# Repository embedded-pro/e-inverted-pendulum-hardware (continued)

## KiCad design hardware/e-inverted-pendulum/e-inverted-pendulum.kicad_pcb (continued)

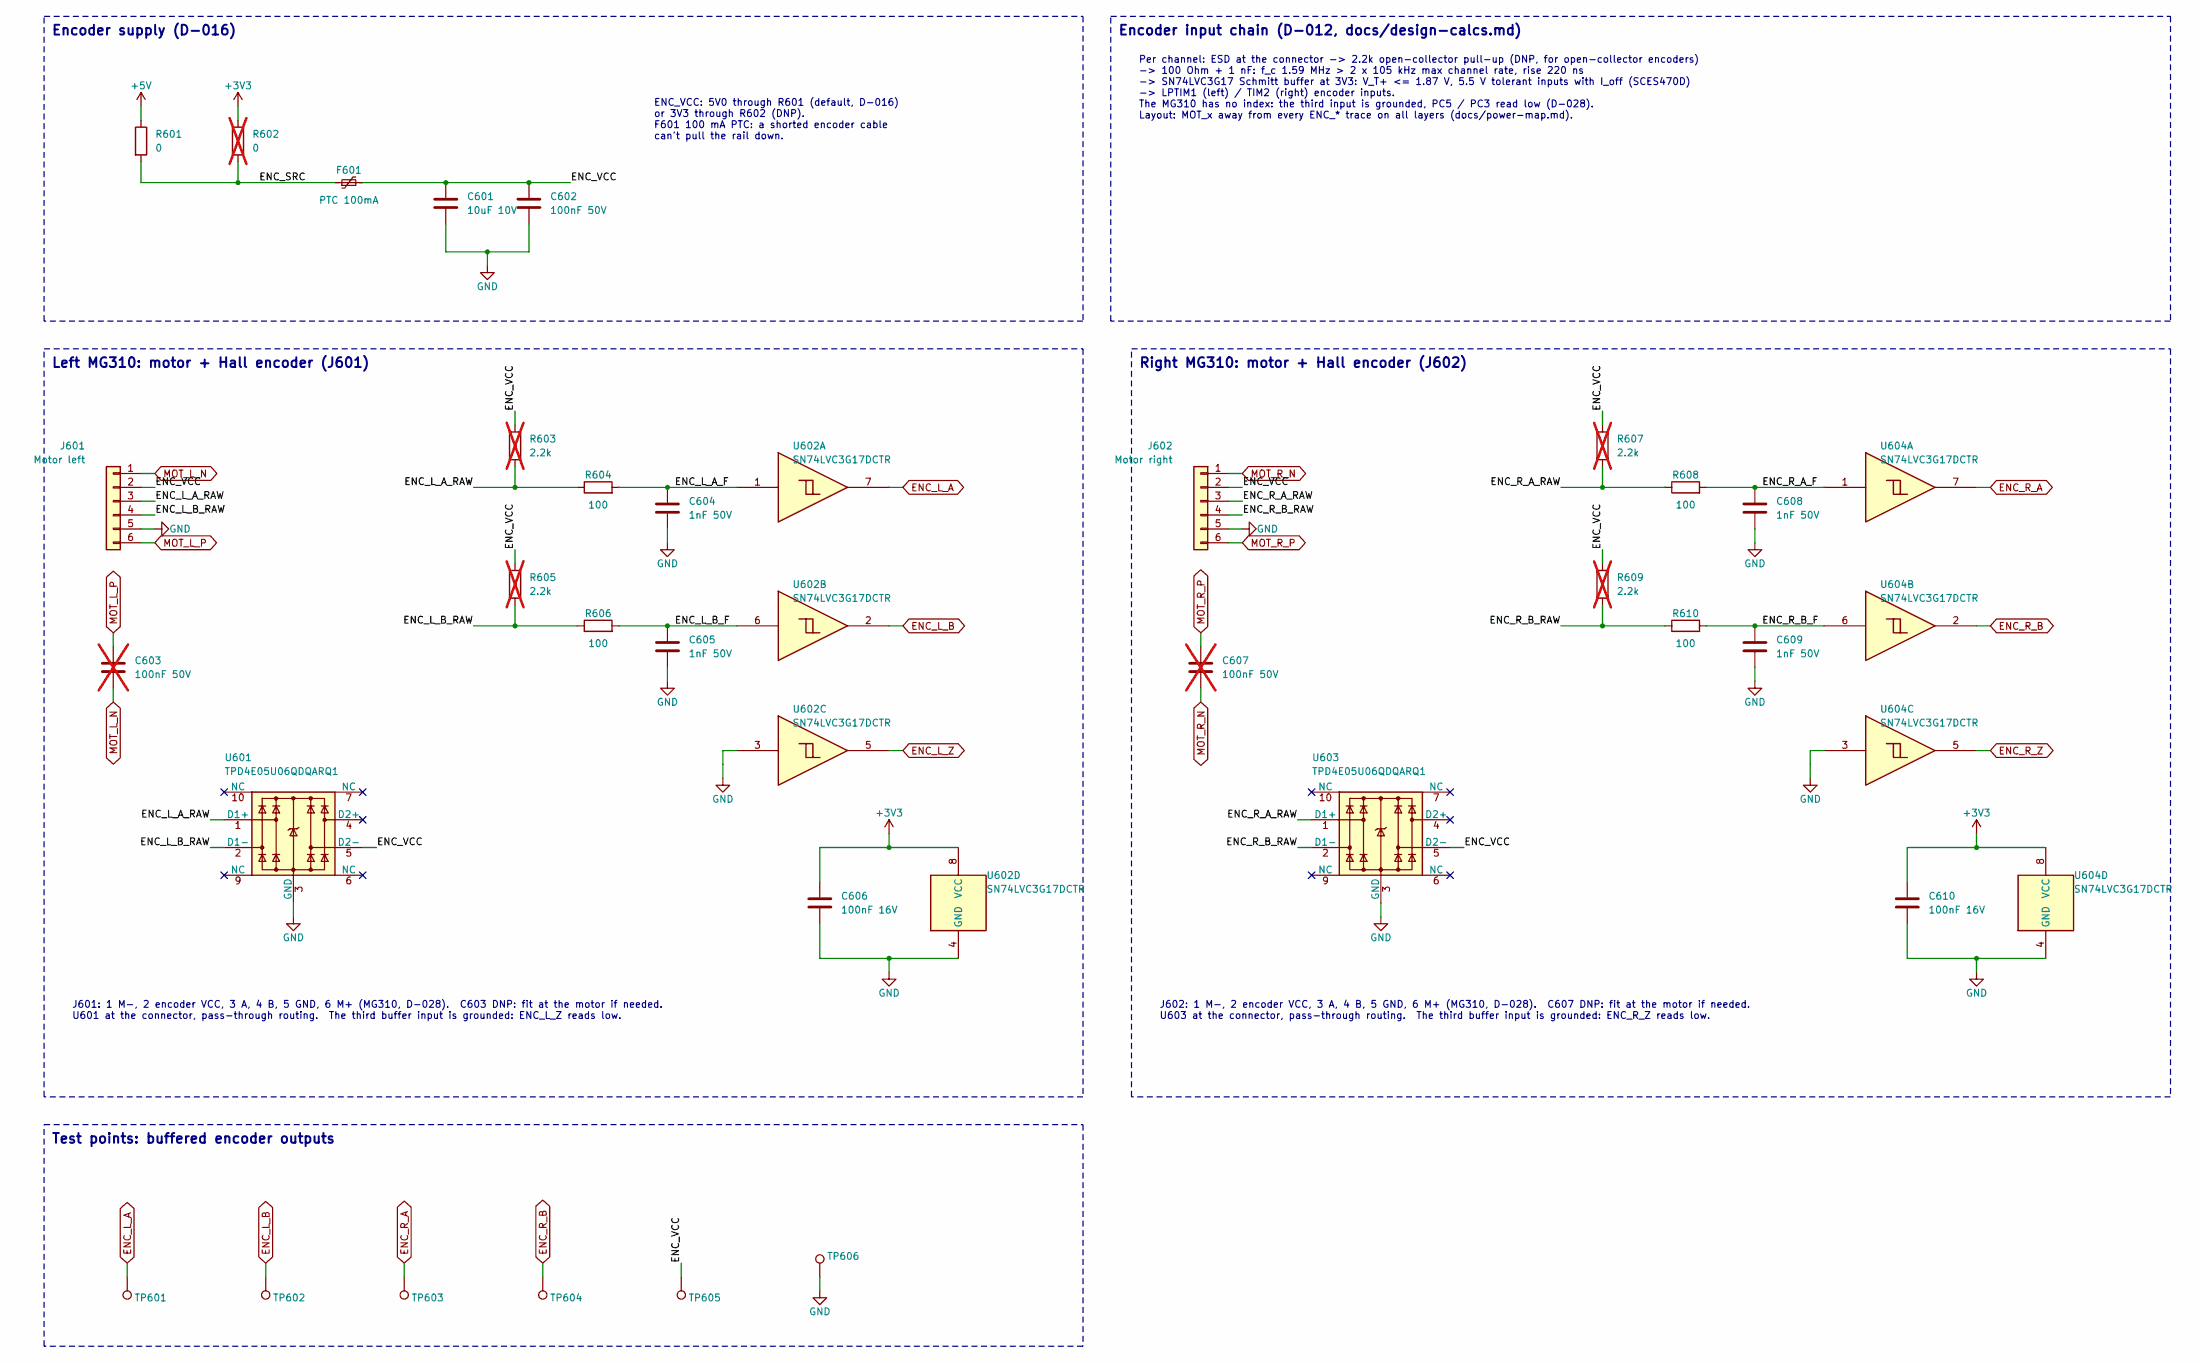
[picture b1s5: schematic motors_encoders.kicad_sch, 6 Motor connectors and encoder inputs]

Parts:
C601: 10uF 10V; C_0603_1608Metric; MPN CL10A106KP8NNNC; LCSC C19702
C602: 100nF 50V; C_0603_1608Metric; MPN CC0603KRX7R9BB104; LCSC C14663
C603, C607: 100nF 50V; C_0603_1608Metric; MPN CC0603KRX7R9BB104; LCSC C14663; not fitted
C604, C605, C608, C609: 1nF 50V; C_0603_1608Metric; MPN CL10B102KB8NNNC; LCSC C1588
C606, C610: 100nF 16V; C_0402_1005Metric; MPN CL05B104KO5NNNC; LCSC C1525
F601: PTC 100mA; Fuse_0805_2012Metric; MPN SMD0805P010TF; LCSC C20975
J601: Motor left; JST_PH_S6B-PH-K_1x06_P2.00mm_Horizontal; MPN S6B-PH-K-S(LF)(SN); LCSC C157920
J602: Motor right; JST_PH_S6B-PH-K_1x06_P2.00mm_Horizontal; MPN S6B-PH-K-S(LF)(SN); LCSC C157920
R601: 0; R_0603_1608Metric; MPN 0603WAF0000T5E; LCSC C21189
R602: 0; R_0603_1608Metric; MPN 0603WAF0000T5E; LCSC C21189; not fitted
R603, R605, R607, R609: 2.2k; R_0603_1608Metric; MPN 0603WAF2201T5E; LCSC C4190; not fitted
R604, R606, R608, R610: 100; R_0603_1608Metric; MPN 0603WAF1000T5E; LCSC C22775
TP601: ENC_L_A; TestPoint_Pad_D1.0mm
TP602: ENC_L_B; TestPoint_Pad_D1.0mm
TP603: ENC_R_A; TestPoint_Pad_D1.0mm
TP604: ENC_R_B; TestPoint_Pad_D1.0mm
TP605: ENC_VCC; TestPoint_Pad_D1.5mm
TP606: GND; TestPoint_Pad_D1.5mm
U601, U603: TPD4E05U06QDQARQ1; USON-10_2.5x1.0mm_P0.5mm; MPN TPD4E05U06QDQARQ1; LCSC C81353
U602, U604: SN74LVC3G17DCTR; SSOP-8_2.95x2.8mm_P0.65mm; MPN SN74LVC3G17DCTR; LCSC C18213

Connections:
+3V3: C606.1, C610.1, R602.1, U602.8 (VCC), U604.8 (VCC); also elsewhere on the board
+5V: R601.1; also elsewhere on the board
/6 Motor connectors and encoder inputs/ENC_L_A_F: C604.1, R604.2, U602.1
/6 Motor connectors and encoder inputs/ENC_L_A_RAW: J601.3, R603.1, R604.1, U601.1 (D1+)
/6 Motor connectors and encoder inputs/ENC_L_B_F: C605.1, R606.2, U602.6
/6 Motor connectors and encoder inputs/ENC_L_B_RAW: J601.4, R605.1, R606.1, U601.2 (D1-)
/6 Motor connectors and encoder inputs/ENC_R_A_F: C608.1, R608.2, U604.1
/6 Motor connectors and encoder inputs/ENC_R_A_RAW: J602.3, R607.1, R608.1, U603.1 (D1+)
/6 Motor connectors and encoder inputs/ENC_R_B_F: C609.1, R610.2, U604.6
/6 Motor connectors and encoder inputs/ENC_R_B_RAW: J602.4, R609.1, R610.1, U603.2 (D1-)
/6 Motor connectors and encoder inputs/ENC_SRC: F601.1, R601.2, R602.2
/6 Motor connectors and encoder inputs/ENC_VCC: C601.1, C602.1, F601.2, J601.2, J602.2, R603.2, R605.2, R607.2, R609.2, TP605.1, U601.5 (D2-), U603.5 (D2-)
ENC_L_A: TP601.1, U602.7; also elsewhere on the board
ENC_L_B: TP602.1, U602.2; also elsewhere on the board
ENC_L_Z: U602.5; also elsewhere on the board
ENC_R_A: TP603.1, U604.7; also elsewhere on the board
ENC_R_B: TP604.1, U604.2; also elsewhere on the board
ENC_R_Z: U604.5; also elsewhere on the board
GND: C601.2, C602.2, C604.2, C605.2, C606.2, C608.2, C609.2, C610.2, J601.5, J602.5, TP606.1, U601.3 (GND), U601.8 (GND), U602.3, U602.4 (GND), U603.3 (GND), U603.8 (GND), U604.3, U604.4 (GND); also elsewhere on the board
MOT_L_N: C603.2, J601.1; also elsewhere on the board
MOT_L_P: C603.1, J601.6; also elsewhere on the board
MOT_R_N: C607.2, J602.1; also elsewhere on the board
MOT_R_P: C607.1, J602.6; also elsewhere on the board

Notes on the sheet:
Per channel: ESD at the connector -> 2.2k open-collector pull-up (DNP, for open-collector encoders) -> 100 Ohm + 1 nF: f_c 1.59 MHz > 2 x 105 kHz max channel rate, rise 220 ns -> SN74LVC3G17 Schmitt buffer at 3V3: V_T+ <= 1.87 V, 5.5 V tolerant inputs with I_off (SCES470D) -> LPTIM1 (left) / TIM2 (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
Right MG310: motor + Hall encoder (J602)
J602: 1 M-, 2 encoder VCC, 3 A, 4 B, 5 GND, 6 M+ (MG310, D-028). C607 DNP: fit at the motor if needed. U603 at the connector, pass-through routing. The third buffer input is grounded: ENC_R_Z reads low.
J601: 1 M-, 2 encoder VCC, 3 A, 4 B, 5 GND, 6 M+ (MG310, D-028). C603 DNP: fit at the motor if needed. U601 at the connector, pass-through routing. The third buffer input is grounded: ENC_L_Z reads low.
Encoder input chain (D-012, docs/design-calcs.md)
ENC_VCC: 5V0 through R601 (default, D-016) or 3V3 through R602 (DNP). F601 100 mA PTC: a shorted encoder cable can't pull the rail down.
Left MG310: motor + Hall encoder (J601)
Test points: buffered encoder outputs
Encoder supply (D-016)

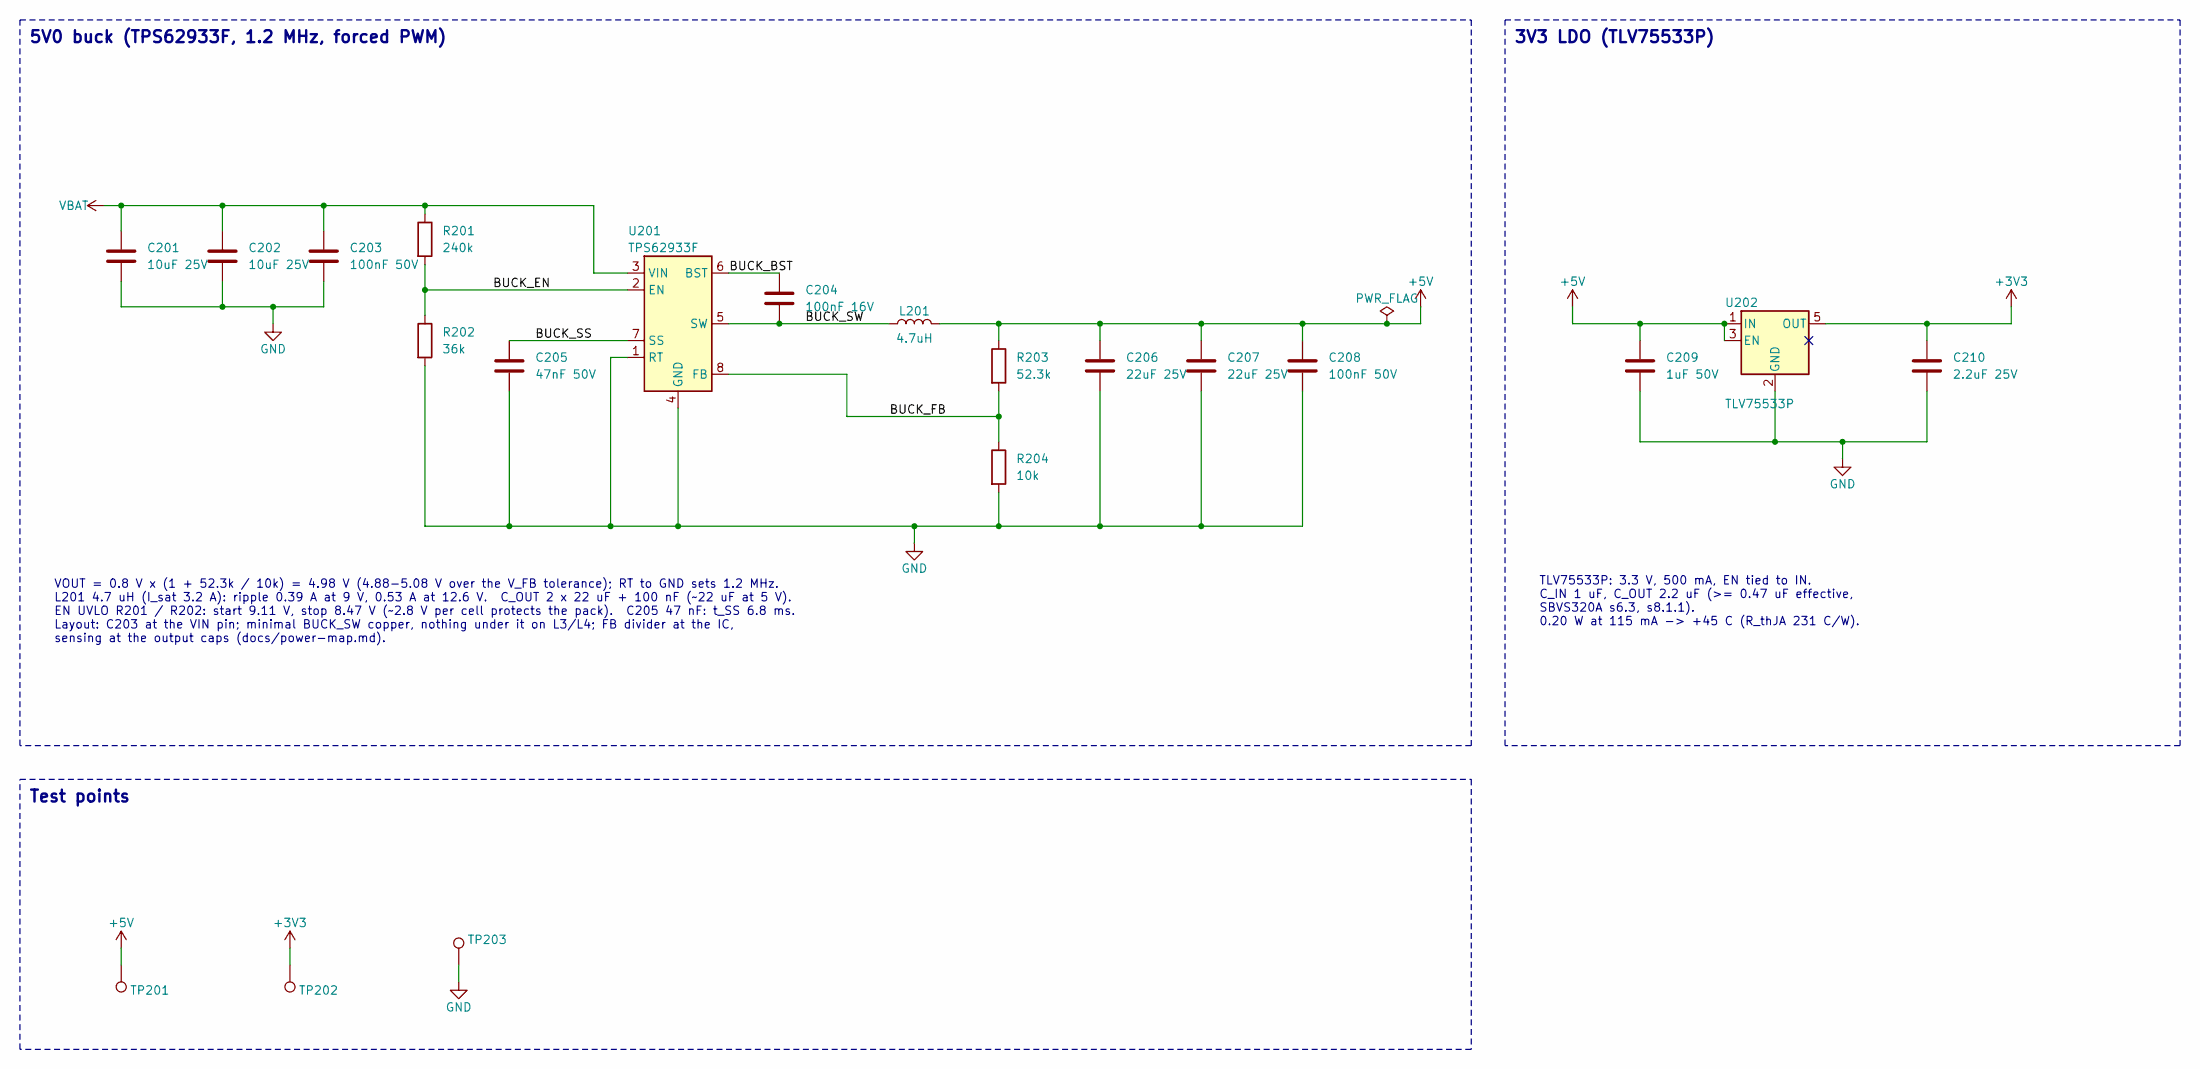
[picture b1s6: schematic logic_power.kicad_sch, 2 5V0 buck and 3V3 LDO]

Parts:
C201, C202: 10uF 25V; C_0805_2012Metric; MPN CL21A106KAYNNNE; LCSC C15850
C203, C208: 100nF 50V; C_0603_1608Metric; MPN CC0603KRX7R9BB104; LCSC C14663
C204: 100nF 16V; C_0402_1005Metric; MPN CL05B104KO5NNNC; LCSC C1525
C205: 47nF 50V; C_0603_1608Metric; MPN CL10B473KB8NNNC; LCSC C1622
C206, C207: 22uF 25V; C_0805_2012Metric; MPN CL21A226MAQNNNE; LCSC C45783
C209: 1uF 50V; C_0603_1608Metric; MPN CL10A105KB8NNNC; LCSC C15849
C210: 2.2uF 25V; C_0603_1608Metric; MPN CL10A225KO8NNNC; LCSC C23630
L201: 4.7uH; L_Sunlord_SWPA4030S; MPN SWPA4030S4R7MT; LCSC C57269
R201: 240k; R_0603_1608Metric; MPN 0603WAF2403T5E; LCSC C4197
R202: 36k; R_0603_1608Metric; MPN 0603WAF3602T5E; LCSC C23147
R203: 52.3k; R_0603_1608Metric; MPN 0603WAF5232T5E; LCSC C23198
R204: 10k; R_0603_1608Metric; MPN 0603WAF1002T5E; LCSC C25804
TP201: +5V; TestPoint_Pad_D1.5mm
TP202: +3V3; TestPoint_Pad_D1.5mm
TP203: GND; TestPoint_Pad_D1.5mm
U201: TPS62933F; SOT-583-8; MPN TPS62933FDRLR; LCSC C5219272
U202: TLV75533P; SOT-23-5; MPN TLV75533PDBVR; LCSC C404027

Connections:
+3V3: C210.1, TP202.1, U202.5 (OUT); also elsewhere on the board
+5V: C206.1, C207.1, C208.1, C209.1, L201.2, R203.1, TP201.1, U202.1 (IN), U202.3 (EN); also elsewhere on the board
/2 5V0 buck and 3V3 LDO/BUCK_BST: C204.1, U201.6 (BST)
/2 5V0 buck and 3V3 LDO/BUCK_EN: R201.2, R202.1, U201.2 (EN)
/2 5V0 buck and 3V3 LDO/BUCK_FB: R203.2, R204.1, U201.8 (FB)
/2 5V0 buck and 3V3 LDO/BUCK_SS: C205.1, U201.7 (SS)
/2 5V0 buck and 3V3 LDO/BUCK_SW: C204.2, L201.1, U201.5 (SW)
GND: C201.2, C202.2, C203.2, C205.2, C206.2, C207.2, C208.2, C209.2, C210.2, R202.2, R204.2, TP203.1, U201.1 (RT), U201.4 (GND), U202.2 (GND); also elsewhere on the board
VBAT: C201.1, C202.1, C203.1, R201.1, U201.3 (VIN); also elsewhere on the board

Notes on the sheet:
VOUT = 0.8 V x (1 + 52.3k / 10k) = 4.98 V (4.88-5.08 V over the V_FB tolerance); RT to GND sets 1.2 MHz. L201 4.7 uH (I_sat 3.2 A): ripple 0.39 A at 9 V, 0.53 A at 12.6 V. C_OUT 2 x 22 uF + 100 nF (~22 uF at 5 V). EN UVLO R201 / R202: start 9.11 V, stop 8.47 V (~2.8 V per cell protects the pack). C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
3V3 LDO (TLV75533P)
TLV75533P: 3.3 V, 500 mA, EN tied to IN. C_IN 1 uF, C_OUT 2.2 uF (>= 0.47 uF effective, SBVS320A s6.3, s8.1.1). 0.20 W at 115 mA -> +45 C (R_thJA 231 C/W).
Test points
5V0 buck (TPS62933F, 1.2 MHz, forced PWM)

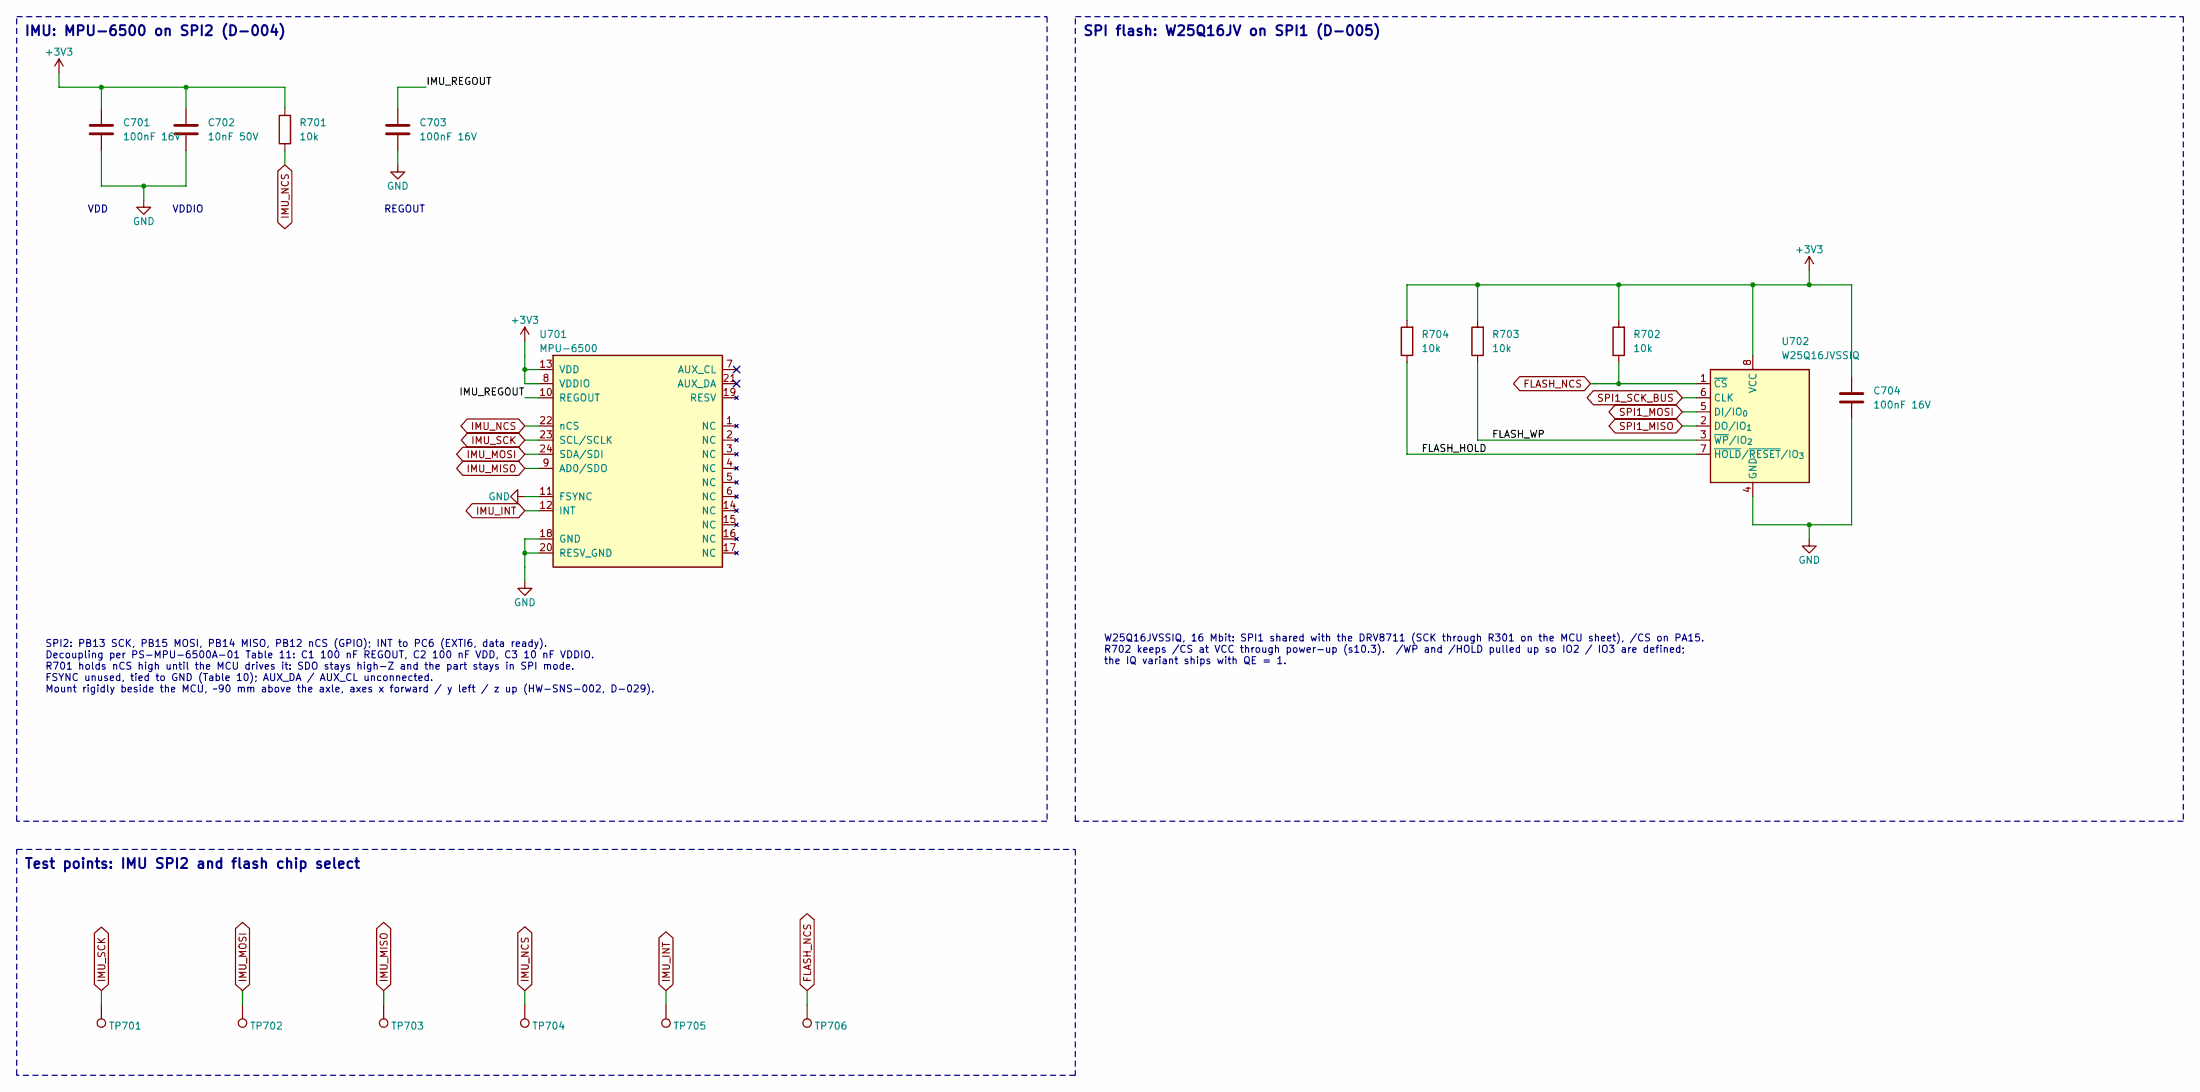
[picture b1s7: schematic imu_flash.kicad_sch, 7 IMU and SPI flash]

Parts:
C701, C703, C704: 100nF 16V; C_0402_1005Metric; MPN CL05B104KO5NNNC; LCSC C1525
C702: 10nF 50V; C_0603_1608Metric; MPN CL10B103KB8NNNC; LCSC C1589
R701, R702, R703, R704: 10k; R_0603_1608Metric; MPN 0603WAF1002T5E; LCSC C25804
TP701: IMU_SCK; TestPoint_Pad_D1.0mm
TP702: IMU_MOSI; TestPoint_Pad_D1.0mm
TP703: IMU_MISO; TestPoint_Pad_D1.0mm
TP704: IMU_NCS; TestPoint_Pad_D1.0mm
TP705: IMU_INT; TestPoint_Pad_D1.0mm
TP706: FLASH_NCS; TestPoint_Pad_D1.0mm
U701: MPU-6500; InvenSense_QFN-24_3x3mm_P0.4mm; MPN MPU-6500; LCSC C50278
U702: W25Q16JVSSIQ; SOIC-8_5.3x5.3mm_P1.27mm; MPN W25Q16JVSSIQ; LCSC C131025

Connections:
+3V3: C701.1, C702.1, C704.1, R701.2, R702.2, R703.2, R704.2, U701.8 (VDDIO), U701.13 (VDD), U702.8 (VCC); also elsewhere on the board
/7 IMU and SPI flash/FLASH_HOLD: R704.1, U702.7 (~HOLD/~RESET/IO_{3})
/7 IMU and SPI flash/FLASH_WP: R703.1, U702.3 (~WP/IO_{2})
/7 IMU and SPI flash/IMU_REGOUT: C703.1, U701.10 (REGOUT)
FLASH_NCS: R702.1, TP706.1, U702.1 (~CS); also elsewhere on the board
GND: C701.2, C702.2, C703.2, C704.2, U701.11 (FSYNC), U701.18 (GND), U701.20 (RESV_GND), U702.4 (GND); also elsewhere on the board
IMU_INT: TP705.1, U701.12 (INT); also elsewhere on the board
IMU_MISO: TP703.1, U701.9 (AD0/SDO); also elsewhere on the board
IMU_MOSI: TP702.1, U701.24 (SDA/SDI); also elsewhere on the board
IMU_NCS: R701.1, TP704.1, U701.22 (nCS); also elsewhere on the board
IMU_SCK: TP701.1, U701.23 (SCL/SCLK); also elsewhere on the board
SPI1_MISO: U702.2 (DO/IO_{1}); also elsewhere on the board
SPI1_MOSI: U702.5 (DI/IO_{0}); also elsewhere on the board
SPI1_SCK_BUS: U702.6 (CLK); also elsewhere on the board

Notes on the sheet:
VDD
SPI flash: W25Q16JV on SPI1 (D-005)
W25Q16JVSSIQ, 16 Mbit: SPI1 shared with the DRV8711 (SCK through R301 on the MCU sheet), /CS on PA15. R702 keeps /CS at VCC through power-up (s10.3). /WP and /HOLD pulled up so IO2 / IO3 are defined; the IQ variant ships with QE = 1.
REGOUT
SPI2: PB13 SCK, PB15 MOSI, PB14 MISO, PB12 nCS (GPIO); INT to PC6 (EXTI6, data ready). Decoupling per PS-MPU-6500A-01 Table 11: C1 100 nF REGOUT, C2 100 nF VDD, C3 10 nF VDDIO. R701 holds nCS high until the MCU drives it: SDO stays high-Z and the part stays in SPI mode. FSYNC unused, tied to GND (T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
Test points: IMU SPI2 and flash chip select
VDDIO
IMU: MPU-6500 on SPI2 (D-004)

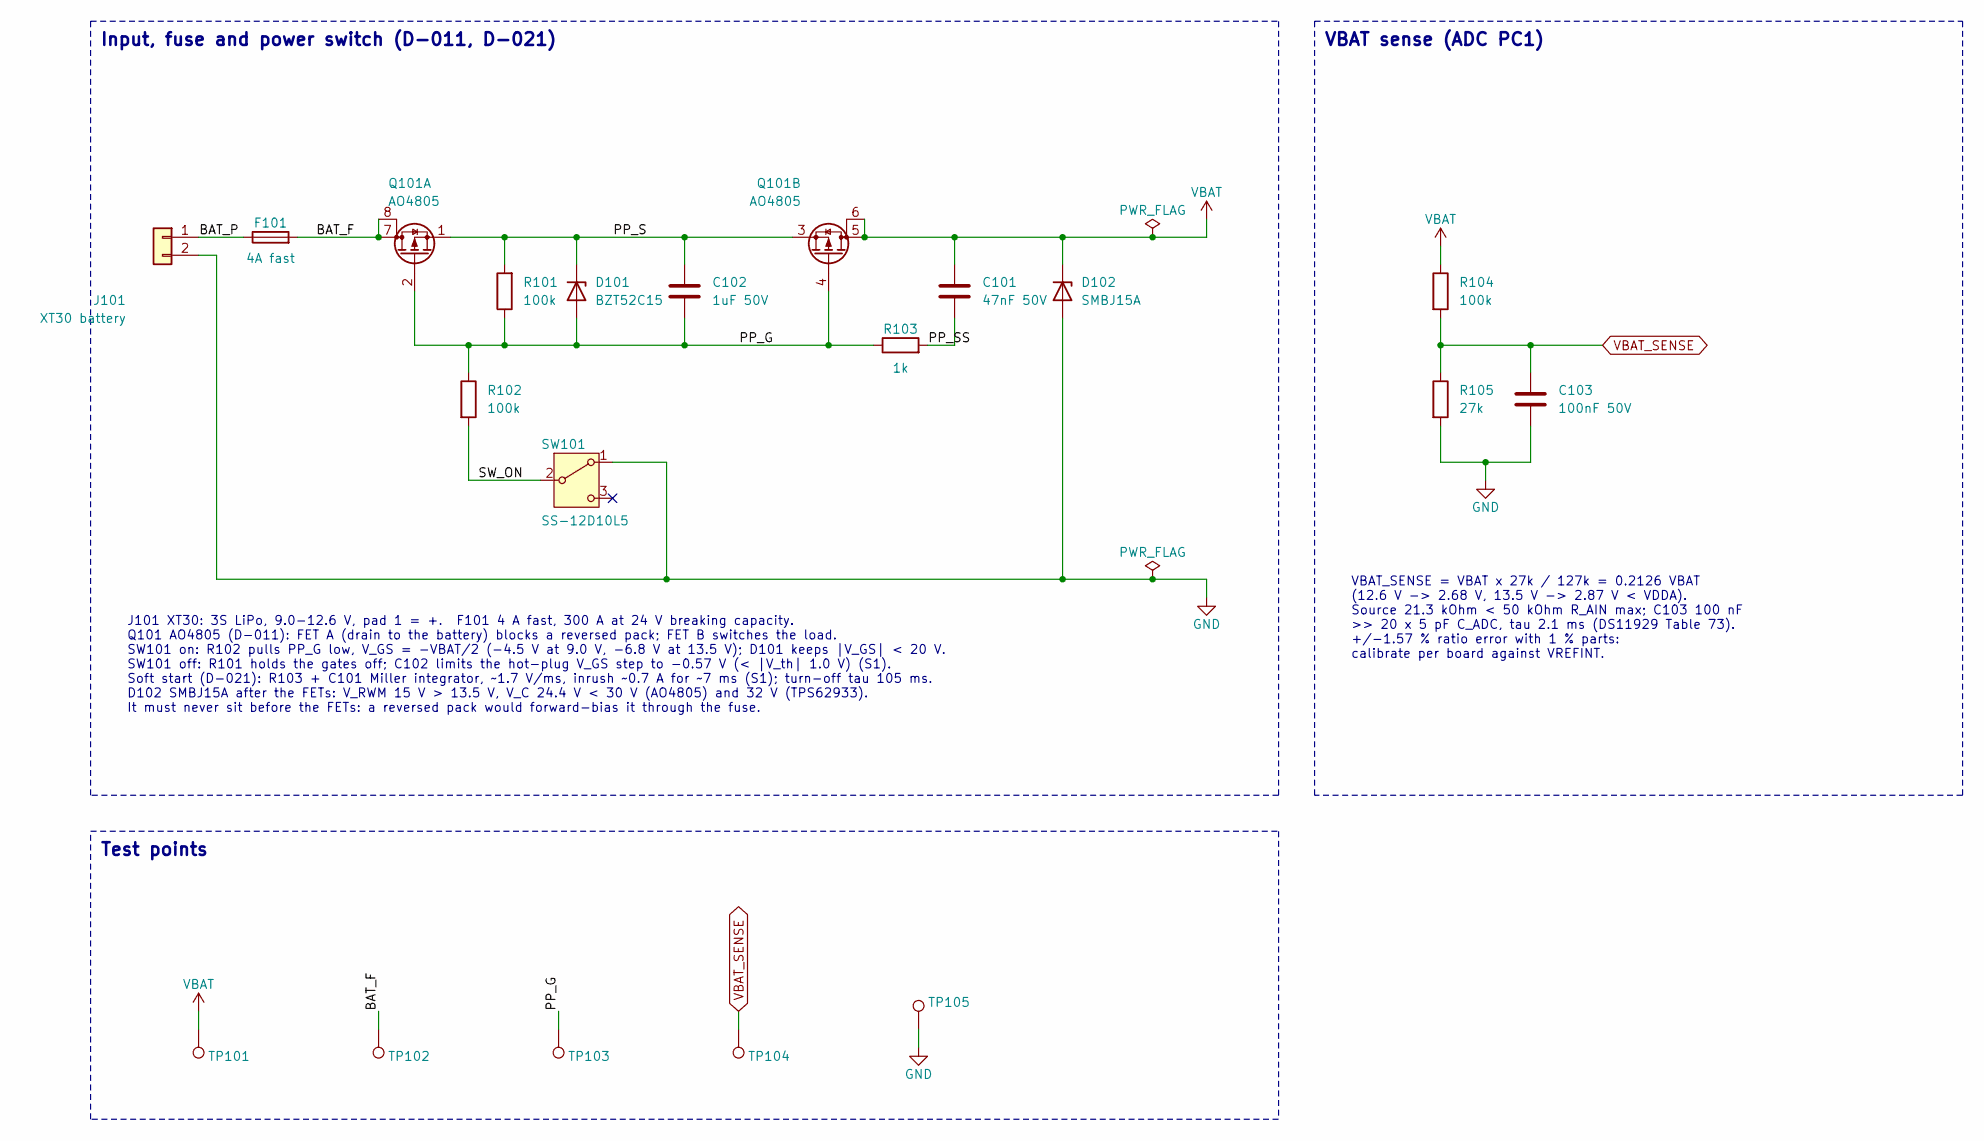
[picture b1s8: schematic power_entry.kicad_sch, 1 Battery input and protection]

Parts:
C101: 47nF 50V; C_0603_1608Metric; MPN CL10B473KB8NNNC; LCSC C1622
C102: 1uF 50V; C_0603_1608Metric; MPN CL10A105KB8NNNC; LCSC C15849
C103: 100nF 50V; C_0603_1608Metric; MPN CC0603KRX7R9BB104; LCSC C14663
D101: BZT52C15; D_SOD-123; MPN BZT52C15; LCSC C2104
D102: SMBJ15A; D_SMB; MPN SMBJ15A; LCSC C83846
F101: 4A fast; Fuse_1206_3216Metric; MPN 1206FA-4A; LCSC C2937379
J101: XT30 battery; AMASS_XT30UPB-F_1x02_P5.00mm_Vertical; MPN XT30UPB-F30.G.Y; LCSC C108769
Q101: AO4805; SOIC-8_3.9x4.9mm_P1.27mm; MPN AO4805; LCSC C3040596
R101, R102, R104: 100k; R_0603_1608Metric; MPN 0603WAF1003T5E; LCSC C25803
R103: 1k; R_0603_1608Metric; MPN 0603WAF1001T5E; LCSC C21190
R105: 27k; R_0603_1608Metric; MPN 0603WAF2702T5E; LCSC C22967
SW101: SS-12D10L5; SW_Slide_SPDT_SS-12D10L5_P4.70mm; MPN SS-12D10L5; LCSC C319012
TP101: VBAT; TestPoint_Pad_D1.5mm
TP102: BAT_F; TestPoint_Pad_D1.0mm
TP103: PP_G; TestPoint_Pad_D1.0mm
TP104: VBAT_SENSE; TestPoint_Pad_D1.0mm
TP105: GND; TestPoint_Pad_D1.5mm

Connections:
/1 Battery input and protection/BAT_F: F101.2, Q101.7 (D), Q101.8 (D), TP102.1
/1 Battery input and protection/BAT_P: F101.1, J101.1
/1 Battery input and protection/PP_G: C102.1, D101.2 (A), Q101.2 (G), Q101.4 (G), R101.1, R102.1, R103.1, TP103.1
/1 Battery input and protection/PP_S: C102.2, D101.1 (K), Q101.1 (S), Q101.3 (S), R101.2
/1 Battery input and protection/PP_SS: C101.1, R103.2
/1 Battery input and protection/SW_ON: R102.2, SW101.2 (B)
GND: C103.2, D102.2 (A), J101.2, R105.2, SW101.1 (A), TP105.1; also elsewhere on the board
VBAT: C101.2, D102.1 (K), Q101.5 (D), Q101.6 (D), R104.1, TP101.1; also elsewhere on the board
VBAT_SENSE: C103.1, R104.2, R105.1, TP104.1; also elsewhere on the board

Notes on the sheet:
J101 XT30: 3S LiPo, 9.0-12.6 V, pad 1 = +. F101 4 A fast, 300 A at 24 V breaking capacity. Q101 AO4805 (D-011): FET A (drain to the battery) blocks a reversed pack; FET B switches the load. SW101 on: R102 pulls PP_G low, V_GS = -VBAT/2 (-4.5 V at 9.0 V, -6.8 V at 13.5 V); D101 keeps |V_GS| < 20 V. 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
Input, fuse and power switch (D-011, D-021)
VBAT sense (ADC PC1)
VBAT_SENSE = VBAT x 27k / 127k = 0.2126 VBAT (12.6 V -> 2.68 V, 13.5 V -> 2.87 V < VDDA). Source 21.3 kOhm < 50 kOhm R_AIN max; C103 100 nF >> 20 x 5 pF C_ADC, tau 2.1 ms (DS11929 Table 73). +/-1.57 % ratio error with 1 % parts: calibrate per board against VREFINT.
Test points

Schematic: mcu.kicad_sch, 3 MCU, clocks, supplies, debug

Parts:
C301, C302, C303, C304, C305, C307, C312, C317: 100nF 16V; C_0402_1005Metric; MPN CL05B104KO5NNNC; LCSC C1525
C306, C309, C314: 4.7uF 10V; C_0402_1005Metric; MPN CL05A475MP5NRNC; LCSC C23733
C308: 100pF 50V; C_0402_1005Metric; MPN CL05C101JB5NNNC; LCSC C26409
C310: 10nF 50V; C_0603_1608Metric; MPN CL10B103KB8NNNC; LCSC C1589
C311, C313: 1uF 50V; C_0603_1608Metric; MPN CL10A105KB8NNNC; LCSC C15849
C315, C316: 6.8pF 50V; C_0402_1005Metric; MPN CL05C6R8CB5NNNC; LCSC C318598
FB301: BLM18PG221SN1D; L_0603_1608Metric; MPN BLM18PG221SN1D; LCSC C80165
J301: STDC14; PinHeader_2x07_P1.27mm_Vertical_SMD; MPN FTSH-107-01-L-DV-K; LCSC C5307809
L301: 10uH; L_0805_2012Metric; MPN LQM21FN100M80L; LCSC C162582
L302: 10nH; L_0402_1005Metric; MPN LQG15HS10NJ02D; LCSC C77103
R301: 33; R_0603_1608Metric; MPN 0603WAF330JT5E; LCSC C23140
R302: 10k; R_0603_1608Metric; MPN 0603WAF1002T5E; LCSC C25804
TP301: NRST; TestPoint_Pad_D1.0mm
TP302: BOOT0; TestPoint_Pad_D1.0mm
TP303: VDDA; TestPoint_Pad_D1.5mm
TP304: VFBSMPS; TestPoint_Pad_D1.0mm
U301: STM32WB55RGV6; QFN-68-1EP_8x8mm_P0.4mm_EP6.4x6.4mm; MPN STM32WB55RGV6; LCSC C401505
Y301: 32MHz; Crystal_SMD_2016-4Pin_2.0x1.6mm; MPN NX2016SA-32MHZ-EXS00A-CS06654; LCSC C5441424
Y302: 32.768kHz; Crystal_SMD_3215-2Pin_3.2x1.5mm; MPN NX3215SA-32.768K-STD-MUA-14; LCSC C156244

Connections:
+3V3: C301.1, C302.1, C303.1, C304.1, C305.1, C306.1, C307.1, C308.1, C309.1, FB301.1, J301.3 (VCC), U301.1 (VBAT), U301.30 (VDD), U301.33 (VDDRF), U301.44 (VDDSMPS), U301.45 (VDD), U301.55 (VDDUSB), U301.68 (VDD); also elsewhere on the board
/3 MCU, clocks, supplies, debug/BOOT0: R302.1, TP302.1, U301.5 (PH3)
/3 MCU, clocks, supplies, debug/HSE_IN: U301.35 (OSC_IN), Y301.1
/3 MCU, clocks, supplies, debug/HSE_OUT: U301.34 (OSC_OUT), Y301.3
/3 MCU, clocks, supplies, debug/NRST: C317.1, J301.12 (~RST), TP301.1, U301.8 (NRST)
/3 MCU, clocks, supplies, debug/OSC32_IN: C315.1, U301.3 (PC14), Y302.1
/3 MCU, clocks, supplies, debug/OSC32_OUT: C316.1, U301.4 (PC15), Y302.2
/3 MCU, clocks, supplies, debug/SMPS_LX: L301.1, U301.43 (VLXSMPS)
/3 MCU, clocks, supplies, debug/SMPS_MID: L301.2, L302.1
/3 MCU, clocks, supplies, debug/SPI1_SCK: R301.1, U301.63 (PB3)
/3 MCU, clocks, supplies, debug/SWCLK: J301.6 (JCLK/SWCLK), U301.56 (PA14)
/3 MCU, clocks, supplies, debug/SWDIO: J301.4 (JTMS/SWDIO), U301.54 (PA13)
/3 MCU, clocks, supplies, debug/VCP_RX: J301.13 (VCP_RX), U301.67 (PB7)
/3 MCU, clocks, supplies, debug/VCP_TX: J301.14 (VCP_TX), U301.66 (PB6)
/3 MCU, clocks, supplies, debug/VFBSMPS: C314.1, L302.2, TP304.1, U301.41 (VFBSMPS)
DRV_AIN1: U301.23 (PA8); also elsewhere on the board
DRV_AIN2: U301.24 (PA9); also elsewhere on the board
DRV_BIN1: U301.51 (PA10); also elsewhere on the board
DRV_BIN2: U301.52 (PA11); also elsewhere on the board
DRV_NFAULT: U301.21 (PA6), U301.25 (PC4); also elsewhere on the board
DRV_NSLEEP: U301.6 (PB8); also elsewhere on the board
DRV_NSTALL: U301.27 (PB2); also elsewhere on the board
DRV_RESET: U301.7 (PB9); also elsewhere on the board
DRV_SCS: U301.19 (PA4); also elsewhere on the board
ENC_L_A: U301.9 (PC0); also elsewhere on the board
ENC_L_B: U301.11 (PC2); also elsewhere on the board
ENC_L_Z: U301.26 (PC5); also elsewhere on the board
ENC_R_A: U301.15 (PA0); also elsewhere on the board
ENC_R_B: U301.16 (PA1); also elsewhere on the board
ENC_R_Z: U301.12 (PC3); also elsewhere on the board
FLASH_NCS: U301.57 (PA15); also elsewhere on the board
GND: C301.2, C302.2, C303.2, C304.2, C305.2, C306.2, C307.2, C308.2, C309.2, C310.2, C311.2, C312.2, C313.2, C314.2, C315.2, C316.2, C317.2, J301.5 (GND), J301.7 (GND), J301.11 (GNDDetect), R302.2, U301.32 (VSSRF), U301.42 (VSSSMPS), U301.69 (VSS), Y301.2 (G), Y301.4 (G); also elsewhere on the board
IMU_INT: U301.50 (PC6); also elsewhere on the board
IMU_MISO: U301.48 (PB14); also elsewhere on the board
IMU_MOSI: U301.49 (PB15); also elsewhere on the board
IMU_NCS: U301.46 (PB12); also elsewhere on the board
IMU_SCK: U301.47 (PB13); also elsewhere on the board
LED_DATA: U301.22 (PA7); also elsewhere on the board
LED_GREEN: U301.38 (PB0); also elsewhere on the board
NFC_GPO: U301.17 (PA2); also elsewhere on the board
QWIIC_SCL: U301.28 (PB10); also elsewhere on the board
QWIIC_SDA: U301.29 (PB11); also elsewhere on the board
RF1: U301.31 (RF1); also elsewhere on the board
SPI1_MISO: U301.64 (PB4); also elsewhere on the board
SPI1_MOSI: U301.65 (PB5); also elsewhere on the board
SPI1_SCK_BUS: R301.2; also elsewhere on the board
VBAT_SENSE: U301.10 (PC1); also elsewhere on the board
VDDA: C310.1, C311.1, C312.1, C313.1, FB301.2, TP303.1, U301.13 (VREF+), U301.14 (VDDA)

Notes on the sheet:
VDD bulk
VDDUSB 55
One 100 nF per supply pin, at the pin, each with its own via; 4.7 uF bulk on VDD. VDDRF 100 nF + 100 pF at pin 33. VDDA and VREF+ through FB301: 10 nF + 1 uF on VDDA, 100 nF + 1 uF on VREF+ (mcu-circuit-design s2). VDDUSB to VDD: USB unused (DS11929 s3.7). VBAT to VDD: no backup domain battery.
Debug and virtual COM port: STDC14 (D-009)
L301 10 uH + L302 10 nH (RX performance) + C314 4.7 uF: DS11929 Table 6. L301 / L302 at pins 41-44, small loop, orthogonal to the RF line (docs/rf.md).
VDDRF 33
VDDSMPS 44
Clocks: HSE 32 MHz, LSE 32.768 kHz
LPTIM1_IN2 EXTI5 TIM2_CH1 TIM2_CH2 EXTI3 USART1_TX USART1_RX GPIO SYS_JTMS-SWDIO SYS_JTCK-SWCLK GPIO ADC1_IN2 TIM17_CH1 I2C3_SCL I2C3_SDA GPIO BOOT0 EXTI2
VDD 68
Core SMPS (DS11929 Table 6)
VREF+ 13
Reset, boot and SPI1 clock termination
VDDA 14
STM32WB55RGV6 (UFQFPN-68)
NRST: 100 nF at the pin (DS11929 Fig. 24); the STDC14 probe drives it too. BOOT0 (PH3): 10k pull-down, no button (D-035): TP302 to +3V3 at reset, or the boot option bytes over SWD. R301 33 Ohm at PB3: source termination of the SCK shared by the DRV8711 and the flash (s9).
Test points
VBAT 1
DRV_AIN1 DRV_AIN2 DRV_BIN1 DRV_BIN2 DRV_NFAULT DRV_NFAULT SPI1_SCK SPI1_MISO SPI1_MOSI DRV_SCS DRV_NSLEEP DRV_RESET IMU_SCK IMU_MISO IMU_MOSI IMU_NCS IMU_INT ENC_L_A
PA8 PA9 PA10 PA11 PA6 PC4 PB3 PB4 PB5 PA4 PB8 PB9 PB13 PB14 PB15 PB12 PC6 PC0
VDD 30
PC2 PC5 PA0 PA1 PC3 PB6 PB7 PB0 PA13 PA14 PA15 PC1 PA7 PB10 PB11 PB2 PH3 PA2
STLINK-V3 STDC14 (1.27 mm): SWD + virtual COM port on USART1 (PB6 TX, PB7 RX). SWO (pin 8) unused: PB3 is SPI1_SCK. Pin 3 is the target VCC reference for the probe.
ENC_L_B ENC_L_Z ENC_R_A ENC_R_B ENC_R_Z VCP_TX VCP_RX LED_GREEN SWDIO SWCLK FLASH_NCS VBAT_SENSE LED_DATA QWIIC_SCL QWIIC_SDA DRV_NSTALL BOOT0 NFC_GPO
Pin plan (pin-data/pinmap.csv, checked by scripts/check_pinmap.py)
HSE NX2016SA: no external caps, load trimmed by HSETUNE (DS11929 Table 5 note 1). LSE NX3215SA, C_L 6 pF: 2 x 6.8 pF C0G (AN2867); LSEDRV = 10, margin ~2.5 (Table 54).
TIM1_CH1 TIM1_CH2 TIM1_CH3 TIM1_CH4 TIM1_BKIN EXTI4 SPI1_SCK SPI1_MISO SPI1_MOSI GPIO GPIO GPIO SPI2_SCK SPI2_MISO SPI2_MOSI GPIO EXTI6 LPTIM1_IN1
Supplies and decoupling (DS11929 Fig. 16)
VDD 45

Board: 4 copper layers, 244 parts (0 on the bottom side), 127 nets, no tracks yet.

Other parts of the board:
MB1, MB2, MB3, MB4: bracket M3; MountingHole_M3_NPTH_KeepOut7mm
MB5, MB6, MB7, MB8: bracket M2; MountingHole_M2_NPTH_KeepOut5.5mm
MC1, MC2, MC3, MC4: battery cradle; MountingHole_M3_NPTH_KeepOut7mm
MH1: bumper; MountingHole_M3_NPTH_KeepOut7mm
MH2: bumper (nylon); MountingHole_M3_NPTH_KeepOut7mm

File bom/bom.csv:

group,function,mpn,lcsc,qty,notes
schematic,MLT-8530,MLT-8530,C94599,1,BZ801
schematic,47nF 50V,CL10B473KB8NNNC,C1622,2,"C101,C205"
schematic,1uF 50V,CL10A105KB8NNNC,C15849,6,"C102,C209,C311,C313,C509,C512"
schematic,100nF 50V,CC0603KRX7R9BB104,C14663,8,"C103,C203,C208,C503,C506,C510,C602,C801"
schematic,10uF 25V,CL21A106KAYNNNE,C15850,4,"C201,C202,C502,C505"
schematic,100nF 16V,CL05B104KO5NNNC,C1525,17,"C204,C301,C302,C303,C304,C305,C307,C312,C317,C511,C606,C610,C701,C703,C704,C802,C803"
schematic,22uF 25V,CL21A226MAQNNNE,C45783,2,"C206,C207"
schematic,2.2uF 25V,CL10A225KO8NNNC,C23630,1,C210
schematic,4.7uF 10V,CL05A475MP5NRNC,C23733,3,"C306,C309,C314"
schematic,100pF 50V,CL05C101JB5NNNC,C26409,1,C308
schematic,10nF 50V,CL10B103KB8NNNC,C1589,3,"C310,C508,C702"
schematic,6.8pF 50V,CL05C6R8CB5NNNC,C318598,2,"C315,C316"
schematic,220u 35V,EEEFK1V221P,C178562,1,C507
schematic,1nF 50V,CL05C102JB5NNNC,C307441,1,C513
schematic,10uF 10V,CL10A106KP8NNNC,C19702,1,C601
schematic,1nF 50V,CL10B102KB8NNNC,C1588,4,"C604,C605,C608,C609"
schematic,BZT52C15,BZT52C15,C2104,1,D101
schematic,SMBJ15A,SMBJ15A,C83846,1,D102
schematic,SS34,SS34,C8678,4,"D501,D502,D503,D504"
schematic,green,KT-0603G,C12624,1,D801
schematic,red,KT-0603R,C2286,1,D802
schematic,1N4148WS,1N4148WS,C2128,1,D803
schematic,4A fast,1206FA-4A,C2937379,1,F101
schematic,PTC 100mA,SMD0805P010TF,C20975,1,F601
schematic,BLM18PG221SN1D,BLM18PG221SN1D,C80165,1,FB301
schematic,MLPF-WB55-01E3,MLPF-WB55-01E3,C2651048,1,FL401
schematic,XT30 battery,XT30UPB-F30.G.Y,C108769,1,J101
schematic,STDC14,FTSH-107-01-L-DV-K,C5307809,1,J301
schematic,"Motor left,Motor right",S6B-PH-K-S(LF)(SN),C157920,2,"J601,J602"
schematic,Qwiic,SM04B-SRSS-TB(LF)(SN),C160404,1,J801
schematic,4.7uH,SWPA4030S4R7MT,C57269,1,L201
schematic,10uH,LQM21FN100M80L,C162582,1,L301
schematic,10nH,LQG15HS10NJ02D,C77103,1,L302
schematic,AO4805,AO4805,C3040596,1,Q101
schematic,CSD88537ND,CSD88537ND,C117439,4,"Q501,Q502,Q503,Q504"
schematic,MMBT3904,MMBT3904,C20526,1,Q801
schematic,100k,0603WAF1003T5E,C25803,3,"R101,R102,R104"
schematic,1k,0603WAF1001T5E,C21190,2,"R103,R303"
schematic,27k,0603WAF2702T5E,C22967,1,R105
schematic,240k,0603WAF2403T5E,C4197,1,R201
schematic,36k,0603WAF3602T5E,C23147,1,R202
schematic,52.3k,0603WAF5232T5E,C23198,1,R203
schematic,10k,0603WAF1002T5E,C25804,12,"R204,R302,R515,R516,R518,R701,R702,R703,R704,R803,R807,R810"
schematic,33,0603WAF330JT5E,C23140,2,"R301,R805"
schematic,0,0402WGF0000TCE,C17168,1,R401
schematic,0,0603WAF0000T5E,C21189,13,"R501,R502,R503,R504,R505,R506,R507,R508,R510,R511,R513,R514,R601"
schematic,50m,HoLR1206-1W-50mR-1%-75ppm,C601102,2,"R509,R512"
schematic,2.2k,0603WAF2201T5E,C4190,3,"R517,R808,R809"
schematic,100,0603WAF1000T5E,C22775,5,"R604,R606,R608,R610,R804"
schematic,470,0603WAF4700T5E,C23179,2,"R801,R806"
schematic,680,0603WAF6800T5E,C23228,1,R802
schematic,SS-12D10L5,SS-12D10L5,C319012,1,SW101
schematic,"BOOT0,USER",TS-1187A-B-A-B,C318884,2,"SW301,SW801"
schematic,TPS62933F,TPS62933FDRLR,C5219272,1,U201
schematic,TLV75533P,TLV75533PDBVR,C404027,1,U202
schematic,STM32WB55RGV6,STM32WB55RGV6,C401505,1,U301
schematic,DRV8711,DRV8711DCPR,C60013,1,U501
schematic,TPD4E05U06DQAR,TPD4E05U06DQAR,C138714,3,"U601,U603,U801"
schematic,SN74LVC3G17DCTR,SN74LVC3G17DCTR,C18213,2,"U602,U604"
schematic,MPU-6500,MPU-6500,C50278,1,U701
schematic,W25Q16JVSSIQ,W25Q16JVSSIQ,C131025,1,U702
schematic,M24C64-RMN6TP,M24C64-RMN6TP,C79988,1,U802
schematic,ST25DV04KC-IE8S3,ST25DV04KC-IE8S3,C5221752,1,U803
schematic,32MHz,NX2016SA-32MHZ-EXS00A-CS06654,C5441424,1,Y301
schematic,32.768kHz,NX3215SA-32.768K-STD-MUA-14,C156244,1,Y302
